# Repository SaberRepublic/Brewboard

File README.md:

# Brewboard
PCB files for the Saber Republic Brewboard

Format is EagleCAD schematic, board layout, and library 

Brewboard is a carrier board for an Arduino Nano, DFPlayer and GY-521 accelerometer. It is designed to make it easy and cheap to build a homebrew soundboard for your saber or other custom props. While it's not as small as other choices on the market it is cheap fully opensource and full-featured. You can use different firmware solutions or roll your own.

 - Connects Arduino Nano, DFPlayer, and GY-521
 - Supports Neo-Pixel and RGB/RGBW Star LEDs and string blades* (with added MOSFETs and resitors)
 - Uses 0805 resitors and sot23 MOSFETs to keep it's footprint small.

You can direct order a board from here:
[Saber Republic](https://saberrepublic.bigcartel.com)

Model Can be viewed and downloaded here:
[Brewboard model](https://sketchfab.com/3d-models/brewboard-v401-b3-2d1b7a565fd34a01af89348552af9d3d?fbclid=IwAR2Z4agn1bq4F1va5oDxdcUzz3cNTd_BFyQfkR_E98XTOAC5beTIbSBYvWw)

There two choices for firmware:

[FX-SaberOS (opensource)](https://github.com/Protonerd/FX-SaberOS)

[STREAM (closedsource but very user friendly)](https://github.com/JakeS0ft/STREAM)

This is a video demo of Brewboard V2 in action.

V2 Pinout diagrams.

For more diagrams and Info Check the [Wiki](https://github.com/SaberRepublic/Brewboard/wiki)

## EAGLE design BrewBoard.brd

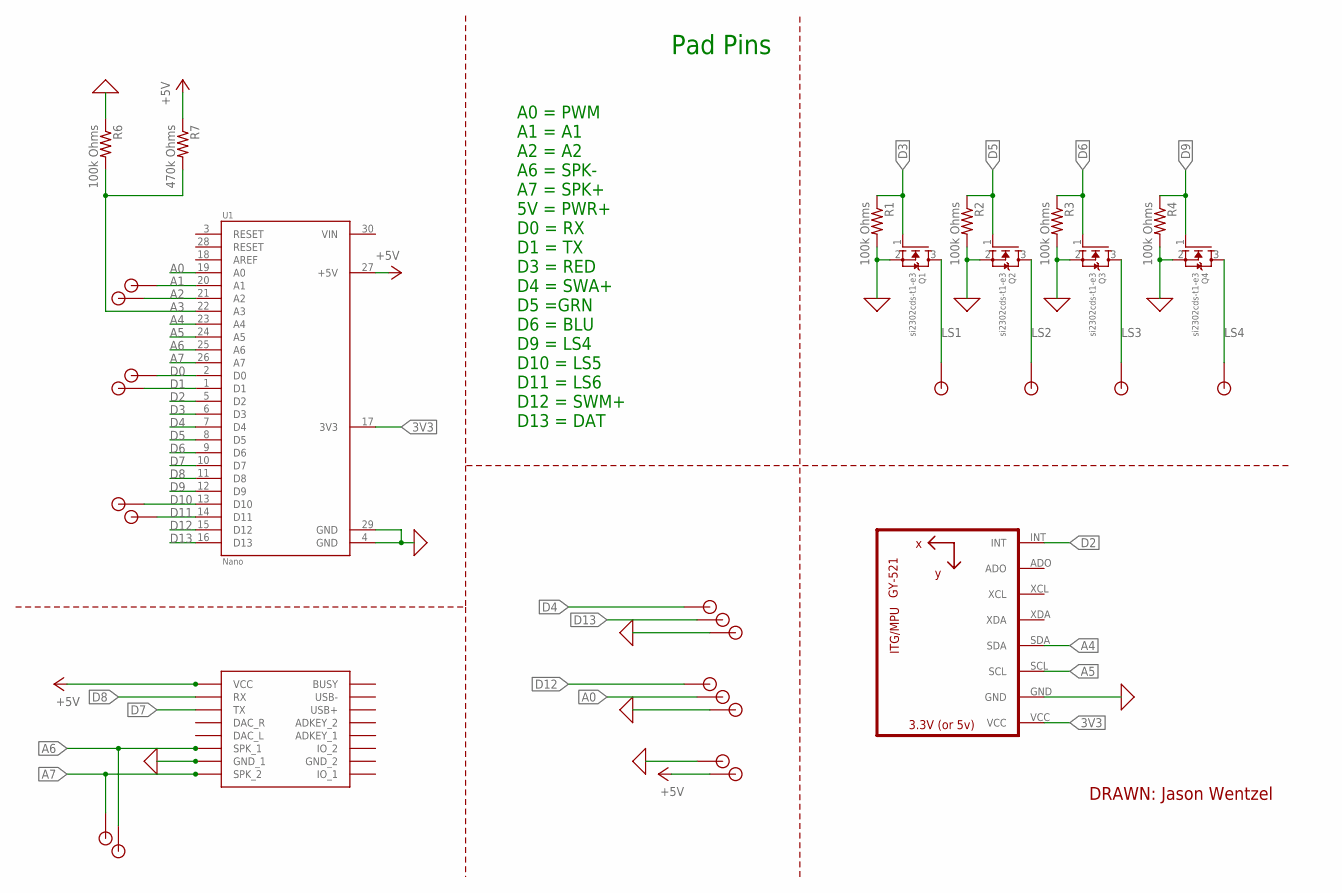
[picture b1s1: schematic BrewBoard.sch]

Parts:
LS1: SINGLE_ONE_SIDE_PAD; SOS_PAD
Q1, Q2, Q3, Q4: si2302cds-t1-e3; SOT23
R1, R2, R3, R4, R6: 100k Ohms; R0805
R7: 470k Ohms; R0805
SPK+: SINGLE_ONE_SIDE_PAD; SOS_PAD
U1: Nano; ARDUINO_NANO_OUT
U2: GY-521MPU6050; GY-521
U3: DFPLAYER
U$1, U$4, U$5, U$6, U$7, U$8, U$9, U$11, U$12, U$13, U$15, U$16, U$17, U$18, U$19, U$22, U$27, U$28: SINGLE_ONE_SIDE_PAD; SOS_PAD

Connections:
0: Q1.2 (S), Q2.2 (S), Q3.2 (S), Q4.2 (S), R1.2, R2.2, R3.2, R4.2, R6.1, U1.4 (GND), U1.29 (GND), U2.GND, U3.GND_1, U$13.P$1, U$17.P$1, U$27.P$1
3V3: U1.17 (3V3), U2.VCC
+5V: R7.1, U1.27 (+5V), U3.VCC, U$12.P$1
A0: U1.19 (A0), U$18.P$1
A1: U1.20 (A1), U$1.P$1
A2: U1.21 (A2), U$4.P$1
A3: R6.2, R7.2, U1.22 (A3)
A4: U1.23 (A4), U2.SDA
A5: U1.24 (A5), U2.SCL
A6: U1.25 (A6), U3.SPK1 (SPK_1), U$11.P$1
A7: SPK+.P$1, U1.26 (A7), U3.SPK2 (SPK_2)
D0: U1.2 (D0), U$5.P$1
D1: U1.1 (D1), U$6.P$1
D2: U1.5 (D2), U2.INT
D3: Q1.1 (G), R1.1, U1.6 (D3)
D4: U1.7 (D4), U$22.P$1
D5: Q2.1 (G), R2.1, U1.8 (D5)
D6: Q3.1 (G), R3.1, U1.9 (D6)
D7: U1.10 (D7), U3.TX
D8: U1.11 (D8), U3.RX
D9: Q4.1 (G), R4.1, U1.12 (D9)
D10: U1.13 (D10), U$8.P$1
D11: U1.14 (D11), U$9.P$1
D12: U1.15 (D12), U$19.P$1
D13: U1.16 (D13), U$28.P$1
LS1: LS1.P$1, Q1.3 (D)
LS2: Q2.3 (D), U$15.P$1
LS3: Q3.3 (D), U$16.P$1
LS4: Q4.3 (D), U$7.P$1
VIN: U1.30 (VIN)

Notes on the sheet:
DRAWN: Jason Wentzel
Pad Pins
A0 = PWM A1 = A1 A2 = A2 A6 = SPK- A7 = SPK+ 5V = PWR+ D0 = RX D1 = TX D3 = RED D4 = SWA+ D5 =GRN D6 = BLU D9 = LS4 D10 = LS5 D11 = LS6 D12 = SWM+ D13 = DAT

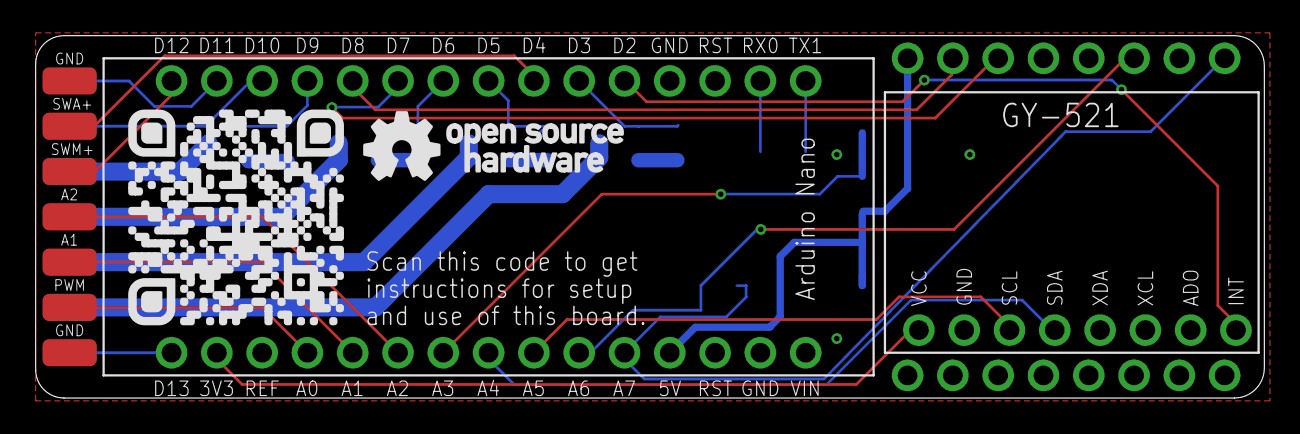
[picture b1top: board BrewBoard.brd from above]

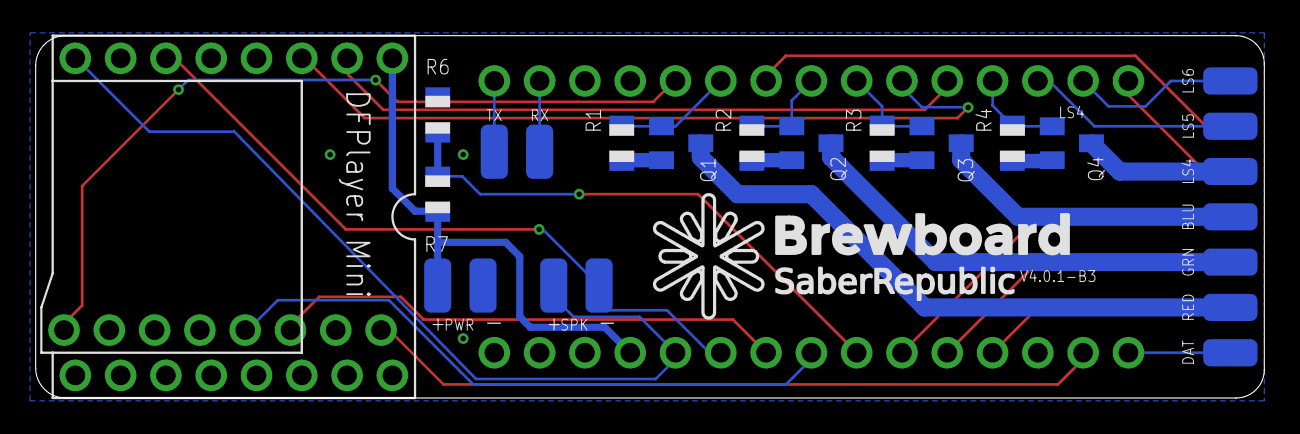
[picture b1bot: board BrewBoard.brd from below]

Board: 2 copper layers, 68.9 x 20.3 mm, 36 parts (24 on the bottom side), 29 nets.

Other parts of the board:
U$2: BREWBOARD_GOLDSTAR_SM
U$3: OSHW_FULL_TOP
U$31: BREWBOARD_QR_CODE

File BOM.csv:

Qty,Value,Device,Package,Parts,Description
5,100k Ohms,R-US_R0805,R0805,"R1, R2, R3, R4, R6","RESISTOR, American symbol"
1,470k Ohms,R-US_R0805,R0805,R7,"RESISTOR, American symbol"
4,si2302cds-t1-e3,MOSFET-NREFLOW,SOT23,"Q1, Q2, Q3, Q4",N-Channel Mosfet

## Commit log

2018-03-05 Update README.md
    A quick description of what Brewboard is.
2018-03-05 Renders
    Adding some renders untill proper boards show up
2018-03-05 Update README.md
    Added a Render of the board
2018-04-11 Pinout diagram
    New pinout diagram
2018-04-12 Adding Links
    Added info via links
2018-04-12 Layout Fixes
    Readme Layout Fixes
2018-04-22 Design Files
    Adding design files for the V2 Brewboard
2018-04-22 Formatting Readme
    Formatting Readme
2018-04-30 Board updated to v2.0.1
    Added thicker traces for Power and Ground
    Added pinout lables
    Updated Read me with Frizting Diagrams for Star and NeoPixel LEDs
2018-04-30 Added version note
    Added version note to OSHPark link
2018-04-30 Added BOM
    Added BOM and Schematic render as well as a small update to the readme.
2018-09-27 Updated BOM
    Updated MOSFETs and added resistor wattage.
2019-03-19 Basic Wiring Diagrams
    New wiring diagrams for documentation.
    Labeling old diagrams as V2 to make it clear what version they are for
2019-03-19 Part Photos
    Added part placment photos
2019-03-19 Logos and Board images
    Added Logos and Board images
2019-03-19 Full Logo
    Added Full Logo
2019-05-29 Brewboard V3 Update
    Adding New Version 3 Update of Brewboard
    Feature/Change List;
    - Interrupt mode is now available for clashes.
    - All extra Pins have pads (for folks that want to experiment and add features).
    - LED Power Traces are now able to handle a total of 7.8A so Pixel Blades can be safely hooked up to MOSFETs (less drain in deepsleep).
    - Power Traces for Pixels removed! Pixel Blade can be wired directly from the battery Positive, and to two or three of the RGB MOSFET pads as mentioned above.
2019-08-17 New 3D Files
    Added Some Suport 3D files for folks that want to design their own chassis systems.
2020-03-06 Added Fritzing files
    Added Fritzing files and one new diagram.
2020-03-07 Fritzing Update
    Replaced single parts with a bin and added bin icons and instructions.
2020-03-08 Fritzing Docs
    Adding Final Step Image
2020-03-08 Renamed
    Renamed with a number for clarity.
2021-05-06 V4 support files
    Brewboard V4 support files
2021-05-06 Update README.md
    added new pdf diagrams to readme
2021-05-06 Update README.md
    replaced PDF diagrams with PNG files
2021-05-06 folder renamed
    Renamed Documentation folder to images which is more accurate
2021-05-06 BOM updated
    Replaced html version of BOM with CSV and Updated for V4
2021-05-06 Readme Updated
    Updated Readme and deleted old readme images
2021-05-06 Updated to V4
    Updated source files to V4 and deleted PDF version of Schematic
2021-05-06 Old Models Removed
    Removed old models and added link to the readme for the new model
2021-05-06 Update README.md
    fixed paths
2021-05-06 Update README.md
    fixed model link
2021-11-05 Added Firmware Links
    Added Firmware Links for both FX-SaberOS and STREAM
2021-11-05 Spacing
    Spacing for links
2021-11-05 spacing
    More spacing...
